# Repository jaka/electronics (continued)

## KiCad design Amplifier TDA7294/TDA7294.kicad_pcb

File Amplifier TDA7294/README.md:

# TDA7294 DIY Audio Power Amplifier Circuit

* EDA: **Kicad 6.0.11**
* PCB dimensions: **71 x 39 mm** (single sided)

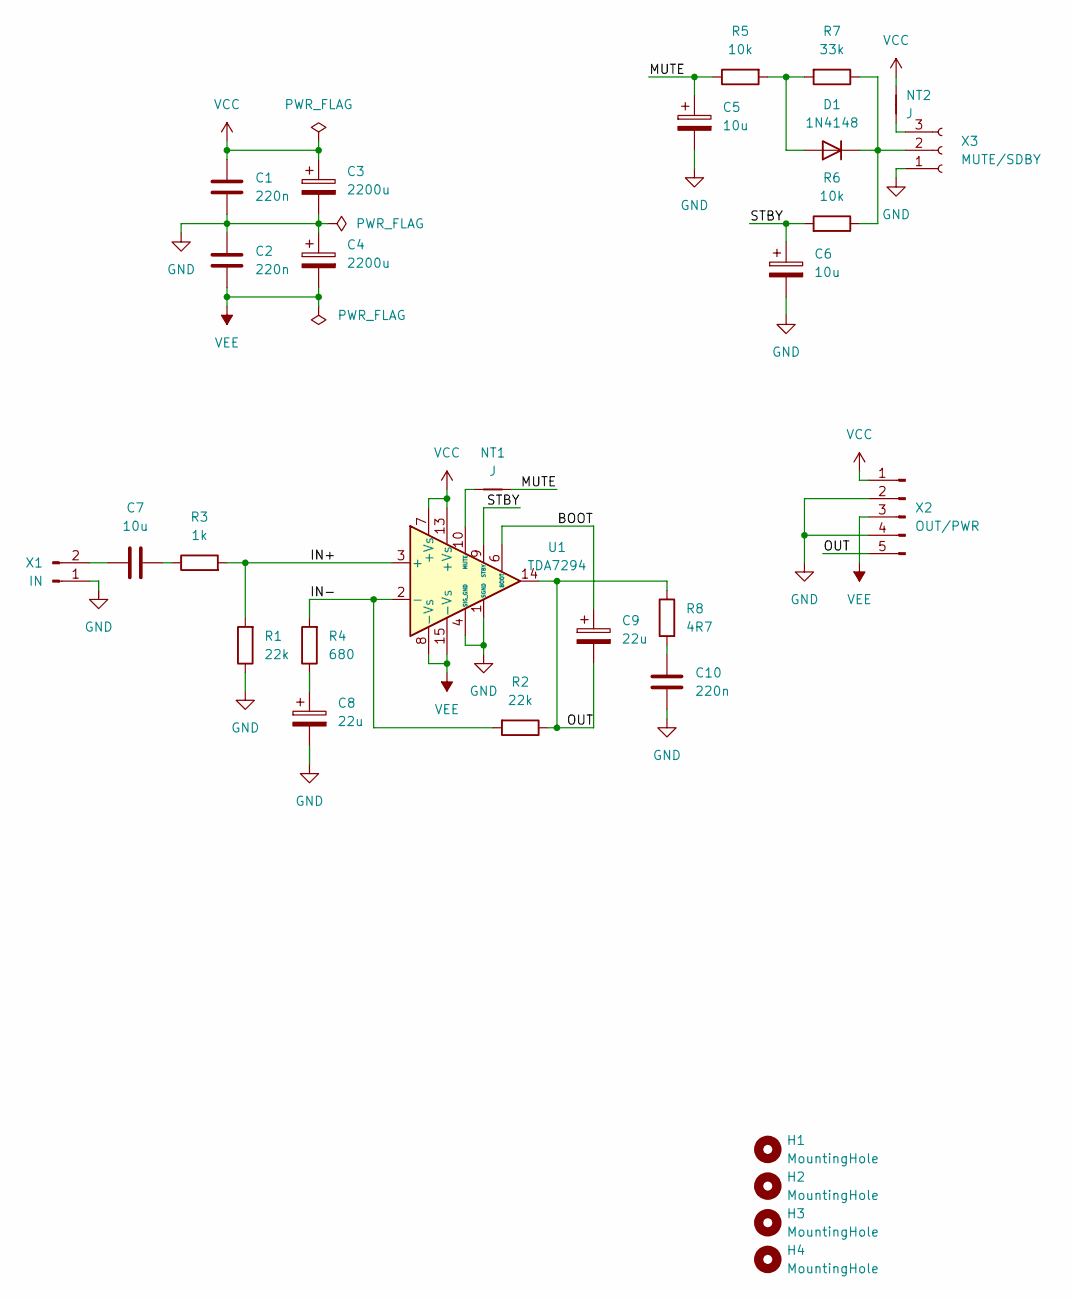
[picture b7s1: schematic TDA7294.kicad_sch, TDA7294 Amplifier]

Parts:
C1, C2, C10: 220n; C_Rect_L7.0mm_W3.5mm_P2.50mm_P5.00mm
C3, C4: 2200u; CP_Radial_D10.0mm_P2.50mm_P5.00mm
C5, C6: 10u; CP_Radial_D6.3mm_P2.50mm
C7: 10u; C_Rect_L7.0mm_W3.5mm_P2.50mm_P5.00mm
C8, C9: 22u; CP_Radial_D6.3mm_P2.50mm
D1: 1N4148; D_DO-35_SOD27_P7.62mm_Horizontal
H1, H2, H3, H4: MountingHole; MountingHole_4.3mm_M4
NT1: J; Wire13mm
NT2: J; Wire4mm
R1, R2: 22k; R_Axial_DIN0207_L6.3mm_D2.5mm_P10.16mm_Horizontal
R3: 1k; R_Axial_DIN0207_L6.3mm_D2.5mm_P10.16mm_Horizontal
R4: 680; R_Axial_DIN0207_L6.3mm_D2.5mm_P10.16mm_Horizontal
R5, R6: 10k; R_Axial_DIN0207_L6.3mm_D2.5mm_P10.16mm_Horizontal
R7: 33k; R_Axial_DIN0207_L6.3mm_D2.5mm_P10.16mm_Horizontal
R8: 4R7; R_Axial_DIN0414_L11.9mm_D4.5mm_P5.08mm_Vertical
U1: TDA7294; TO-220-15_P2.54x2.54mm_StaggerOdd_Lead4.58mm_Vertical
X1: IN; JST_PH_B2B-PH-K_1x02_P2.00mm_Vertical
X2: OUT/PWR; PhoenixContact_MC_1,5_5-G-3.81_1x05_P3.81mm_Horizontal
X3: MUTE/SDBY; JST_PH_B3B-PH-K_1x03_P2.00mm_Vertical

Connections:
/BOOT: C9.1, U1.6 (BOOT)
/IN+: R1.2, R3.2, U1.3 (+)
/IN-: R2.2, R4.2, U1.2 (-)
/MUTE: C5.1, NT1.2, R5.1
/OUT: C9.2, R2.1, R8.1, U1.14, X2.5
/STBY: C6.1, R6.2, U1.9 (STBY)
GND: C1.1, C2.2, C3.2, C4.1, C5.2, C6.2, C8.2, C10.2, R1.1, U1.1 (SGND), U1.4 (SIG_GND), X1.1, X2.2, X2.4, X3.1
unnamed: C7.1, X1.2
unnamed: C7.2, R3.1
unnamed: C8.1, R4.1
unnamed: C10.1, R8.2
unnamed: D1.1 (K), R6.1, R7.1, X3.2
unnamed: D1.2 (A), R5.2, R7.2
unnamed: NT1.1, U1.10 (MUTE)
unnamed: NT2.1, X3.3
VCC: C1.2, C3.1, NT2.2, U1.7 (+Vs), U1.13 (+Vs), X2.1
VEE: C2.1, C4.2, U1.8 (-Vs), U1.15 (-Vs), X2.3

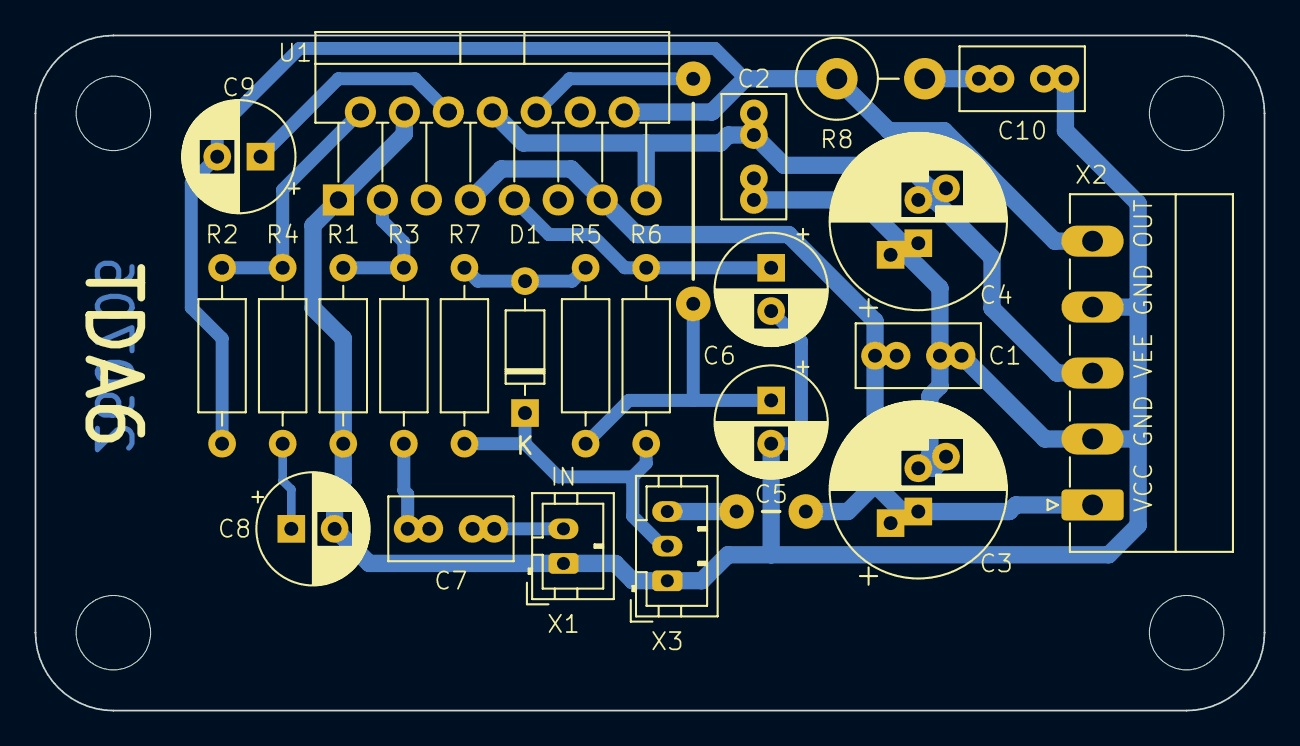
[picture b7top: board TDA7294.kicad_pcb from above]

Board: 2 copper layers, 71.0 x 39.0 mm, 29 parts (0 on the bottom side), 17 nets.

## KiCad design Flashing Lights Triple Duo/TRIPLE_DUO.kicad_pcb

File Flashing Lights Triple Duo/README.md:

# Flashing Lights Triple Duo

This circuit consists of two 555 timers configured at different frequencies. These frequencies are selected so that red LED’s and blue LED’s alternatively flashes. Moreover each group (red or blue) flashes aproximately three times before colour is switched, similar to american police strobe lights. 

* EDA: **Kicad 7.0.11**

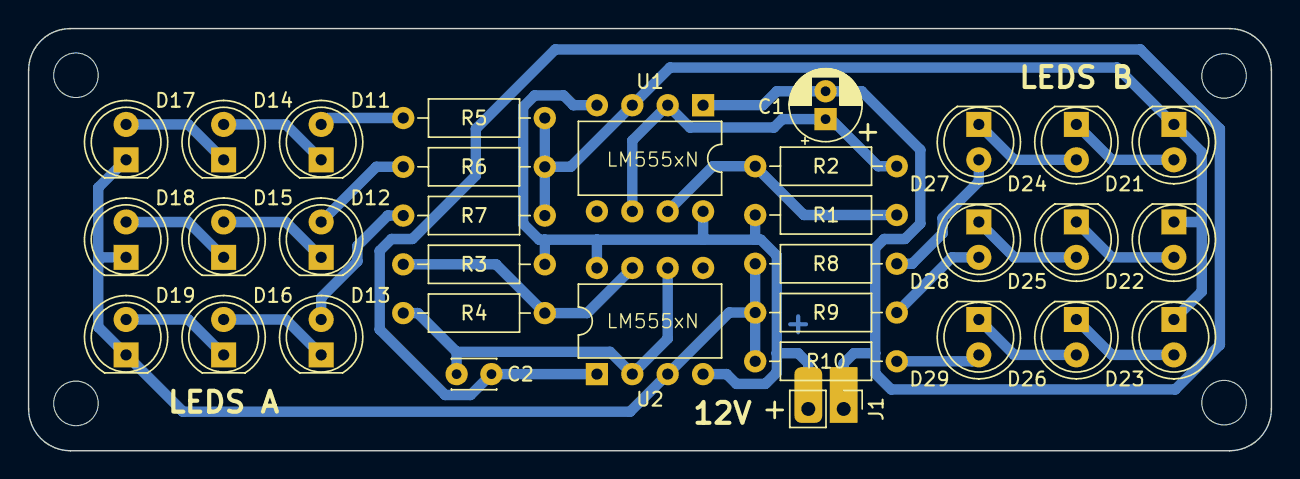
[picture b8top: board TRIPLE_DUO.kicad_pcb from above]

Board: 2 copper layers, 89.2 x 30.3 mm, 33 parts (0 on the bottom side), 26 nets.

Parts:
C1: 10uF; CP_Radial_D5.0mm_P2.00mm
C2: 1uF; C_Disc_D3.0mm_W2.0mm_P2.50mm
D11, D12, D13, D14, D15, D16, D17, D18, D19, D21, D22, D23, D24, D25, D26, D27, D28, D29: LED; LED_D5.0mm
J1: POWER; PinHeader_1x02_P2.54mm_Vertical
R1, R3: 1k; R_Axial_DIN0207_L6.3mm_D2.5mm_P10.16mm_Horizontal
R2: 100k; R_Axial_DIN0207_L6.3mm_D2.5mm_P10.16mm_Horizontal
R4: 330k; R_Axial_DIN0207_L6.3mm_D2.5mm_P10.16mm_Horizontal
R5, R6, R7: 270; R_Axial_DIN0207_L6.3mm_D2.5mm_P10.16mm_Horizontal
R8, R9, R10: 120; R_Axial_DIN0207_L6.3mm_D2.5mm_P10.16mm_Horizontal
U1, U2: LM555xN; DIP-8_W7.62mm

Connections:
/DIS1: R1.1, R2.2, U1.7 (DIS)
/DIS2: R3.1, R4.2, U2.7 (DIS)
/Q1: D21.1 (K), D22.1 (K), D23.1 (K), R5.2, R6.2, R7.2, U1.3 (Q)
/Q2: D17.1 (K), D18.1 (K), D19.1 (K), R8.1, R9.1, R10.1, U2.3 (Q)
/THR1: C1.1, R2.1, U1.2 (TR), U1.6 (THR)
/THR2: C2.1, R4.1, U2.2 (TR), U2.6 (THR)
GND: C1.2, C2.2, J1.1, U1.1 (GND), U2.1 (GND)
unnamed: D11.2 (A), R5.1
unnamed: D11.1 (K), D14.2 (A)
unnamed: D12.2 (A), R6.1
unnamed: D12.1 (K), D15.2 (A)
unnamed: D13.2 (A), R7.1
unnamed: D13.1 (K), D16.2 (A)
unnamed: D14.1 (K), D17.2 (A)
unnamed: D15.1 (K), D18.2 (A)
unnamed: D16.1 (K), D19.2 (A)
unnamed: D21.2 (A), D24.1 (K)
unnamed: D22.2 (A), D25.1 (K)
unnamed: D23.2 (A), D26.1 (K)
unnamed: D24.2 (A), D27.1 (K)
unnamed: D25.2 (A), D28.1 (K)
unnamed: D26.2 (A), D29.1 (K)
unnamed: D27.2 (A), R8.2
unnamed: D28.2 (A), R9.2
unnamed: D29.2 (A), R10.2
VCC: J1.2, R1.2, R3.2, U1.4 (R), U1.8 (VCC), U2.4 (R), U2.8 (VCC)

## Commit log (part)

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2026-06-10 20260610
2026-06-11 20260611
2026-06-12 20260612
2026-06-14 20260614
2026-06-15 20260615
2026-06-27 20260627
